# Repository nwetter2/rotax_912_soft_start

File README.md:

# rotax_912_soft_start
Soft start ignition module for Rotax 900 series engines

All parts [listed in BOM](https://github.com/nwetter2/rotax_912_soft_start/blob/master/BOM.pdf).

Older versions of the Rotax 900 series engines are prone to kickback on starting, which is violent and damaging to the engine. This project, inspired by a similar project by [Turbo-Tom at Rotary Wing Forums](https://www.rotaryforum.com/threads/soft-start-unit-for-rotax-912uls.23381/), improves the issue by ensuring retarded timings are used during start. It accomplishes this by using a relay to introduce a diode in parallel with the timing coil, which filters out the advanced timing pulse, which is opposite the polarity of the retarded timing pulse. Note that Turbo-Tom's design introduces the diode in series with the coil, and this did not work in testing by this project.

The design is quite simple and uses through-hole components to ease construction. It uses the same connectors as the Rotax ignition system, so one can simply unplug one ignition module and insert the soft start module between it and the timing coils. Then, the disable wire of the opposite ignition module is connected, allowing the unmodified ignition circuit to be disabled during start. The mod is also connected to the starter relay and this is what engages the relays during start. A capacitor keeps the relays engaged for 3-8 seconds after starting. Lastly, there is an optional connection for an external indicator, which will be connected to ground while the module is active and left floating when not.

The enclosure is bolted to the top of the existing ignition modules, using longer M5 bolts and washers. The enclosure needs to be modified to accept the larger diameter bolts, and holes added for the wires to pass through. It is recommended to waterproof the pcb after assembly, using the silicone conformal coat listed in the BOM. Loctite 221 or 222 should be used on the mounting bolts.

## Schematic

## Front

## Back

## Assembled
V1.0; no cover

# Installed
V1.0; no cover

# Before
Signal from the timing coil with the soft start module unengaged

# After
Signal from the timing coil with the soft start module engaged

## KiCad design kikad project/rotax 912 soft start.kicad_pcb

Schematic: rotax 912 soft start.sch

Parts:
C1: CP; cap
D1, D2, D3: D; diode
F1: Fuse; fuse
H1, H2, H3, H4: MountingHole; mounting_hole
J1: BOX; 6_wire_18awg
J2: TRIGR; 6_wire_18awg
J3: GND; wire_18awg_stranded
J4: INDK8; wire_22awg_stranded
J5, J6: KILL; wire_18awg_stranded
J7: START; wire_18awg_stranded
K1, K2: TXD2-12V; Relay_TXD2-12V

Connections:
/12V_BUF: C1.1, D1.1 (K), K1.1 (+), K2.1 (+)
/START: F1.1, J7.1
/START_FUSED: D1.2 (A), F1.2
GND: C1.2, H1.1, H2.1, H3.1, H4.1, J3.1, K1.12 (-), K2.5, K2.8, K2.12 (-)
unnamed: D2.1 (K), K1.5
unnamed: D2.2 (A), J1.3, J2.3
unnamed: D3.1 (K), K1.8
unnamed: D3.2 (A), J1.5, J2.5
unnamed: J1.1, J2.1
unnamed: J1.2, J2.2
unnamed: J1.4, J2.4, K1.4
unnamed: J1.6, J2.6, K1.9
unnamed: J4.1, K2.4
unnamed: J5.1, J6.1, K2.9

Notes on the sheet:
To trigger coils in ignition housing Female connector
To existing ignition box Male connector
Deactivates opposite ignition module
Optional external indicator light
Note: Relays will not deactivate simultaneously

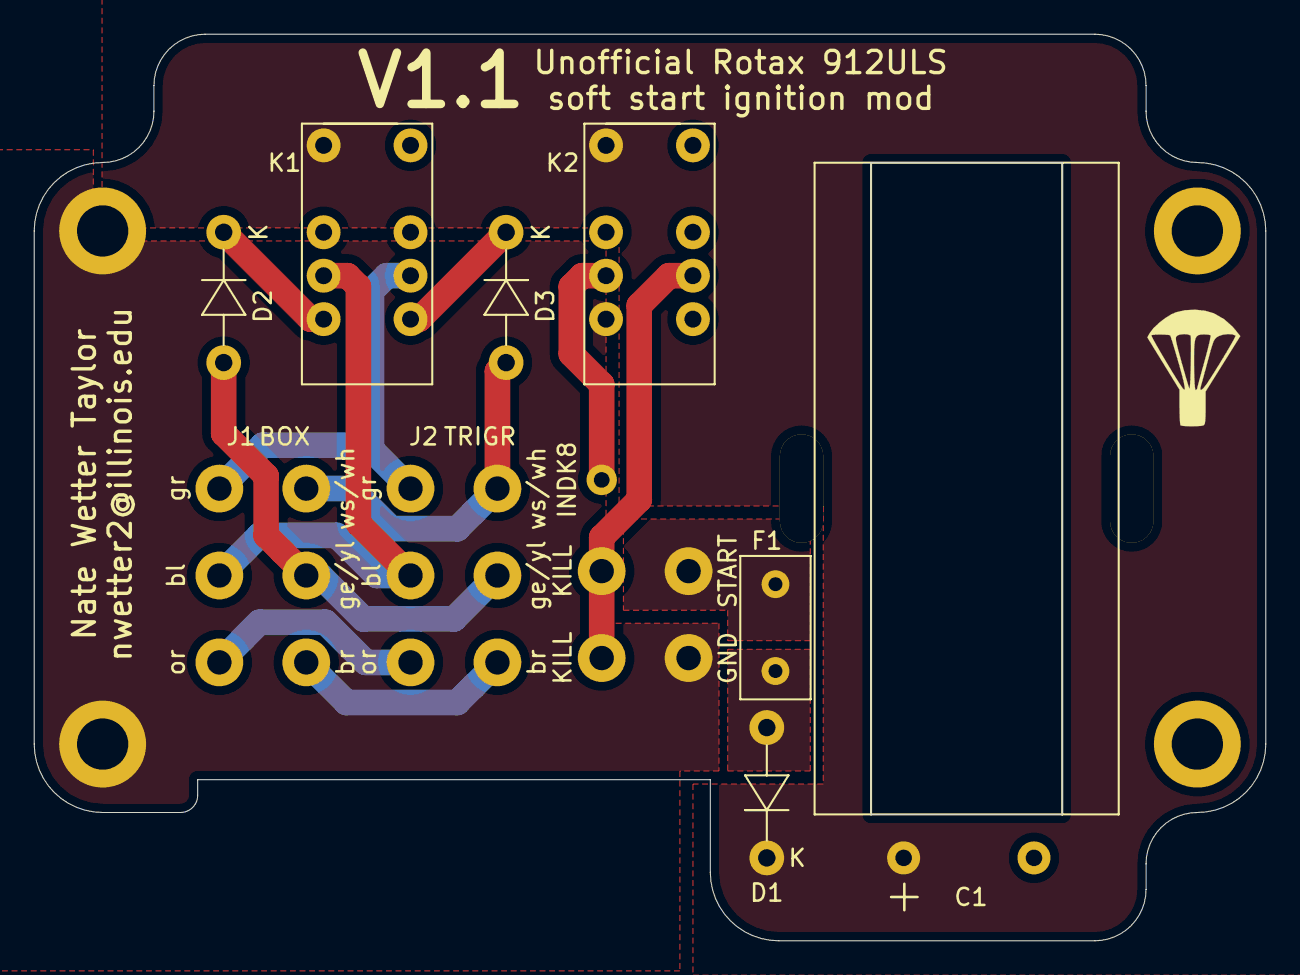
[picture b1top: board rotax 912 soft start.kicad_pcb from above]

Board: 2 copper layers, 72.0 x 53.0 mm, 18 parts (0 on the bottom side), 14 nets.
